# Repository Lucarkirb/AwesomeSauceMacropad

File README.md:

# AWESOME SAUCE MACROPAD

The best worst macropad I have ever made, for the world to see. 
Runs custom firmware that will support almost infinite layers, macros, and maybe even AHK support?

## What the hell is it?
It's a Seeed studio xiao rp2040 macro pad designed like a madman, with custom firmware thats coming real soon. 
The layout is a 3x3 + an extra 3 button thumb cluster that lets you add more common keys like layer shifters or modifiers. It also has an encoder that can work as what you want but also allows you to interact with the firmwares settings, along with an OLED display to do your bidding.

Currently, the project is a mess as the thing requires the KY-040 encoder breakout board instead of just an smt encoder and also requires a generic i2c oled screen you get for your arduinos.

## Can I get it? 
Go order it yourself, tho pcba is going to get pricy since the neo pixels are costly to handle in a factory. Luckily they are super easy to hand solder.

Currently, the project is still being manufactured as im writing this, and thus i dont have any way to write firmware. Stay tuned.

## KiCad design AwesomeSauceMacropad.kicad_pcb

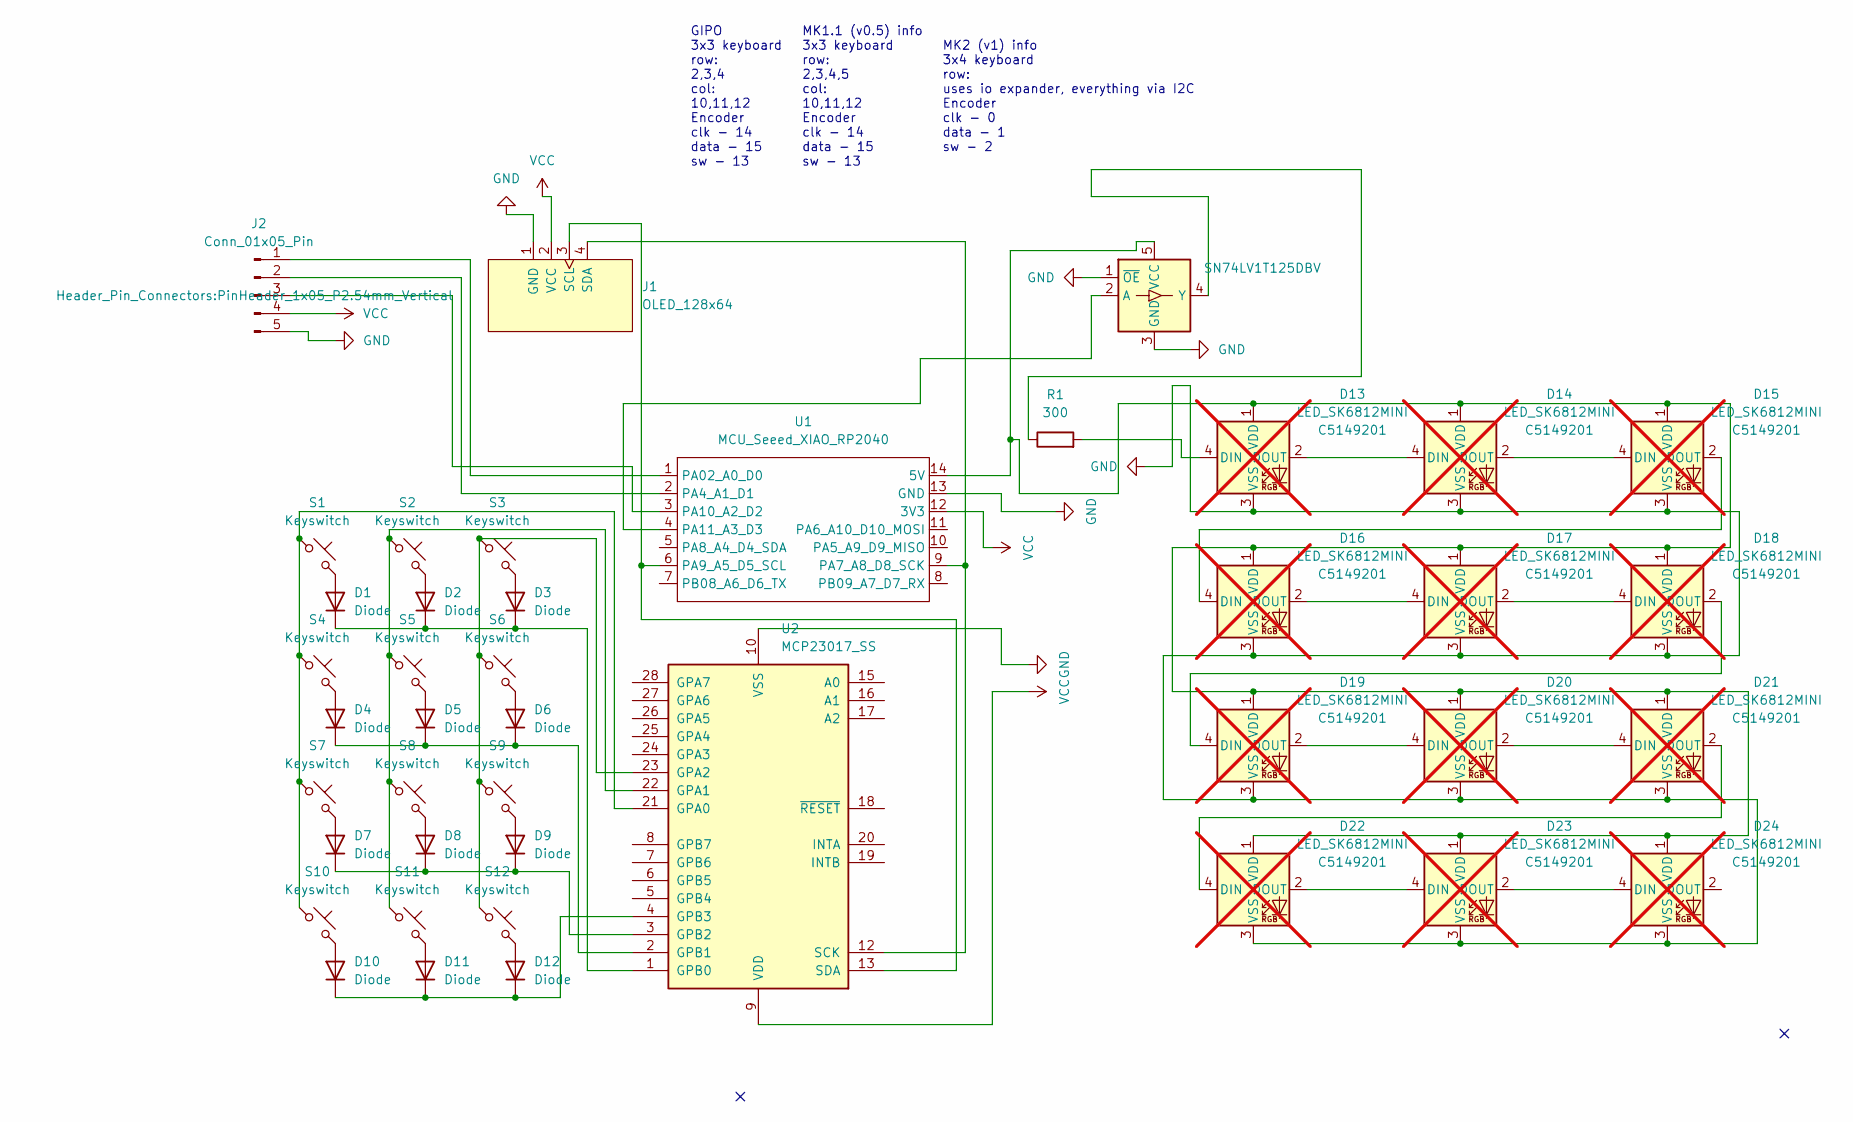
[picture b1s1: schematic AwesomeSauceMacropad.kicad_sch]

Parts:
D1, D2, D3, D4, D5, D6, D7, D8, D9, D10, D11, D12: Diode; Diode_SOD-123
D13, D14, D15, D16, D17, D18, D19, D20, D21, D22, D23, D24: LED_SK6812MINI; LCSC C5149201; not fitted
J1: OLED_128x64
J2: Conn_01x05_Pin; PinHeader_1x05_P2.54mm_Vertical
R1: 300; Resistor_0805
S1, S2, S3, S4, S5, S6, S7, S8, S9, S10, S11, S12: Keyswitch; Hotswap_Choc_V1V2_1.00u
U1: MCU_Seeed_XIAO_RP2040; Seeed_XIAO_RP2040
U2: MCP23017_SS; SSOP-28_5.3x10.2mm_P0.65mm
U3: SN74LV1T125DBV; SOT-23-5

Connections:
GND: D13.3 (VSS), D14.3 (VSS), D15.3 (VSS), D16.3 (VSS), D17.3 (VSS), D18.3 (VSS), D19.3 (VSS), D20.3 (VSS), D21.3 (VSS), D22.3 (VSS), D23.3 (VSS), D24.3 (VSS), J1.1 (GND), J2.5, U1.13 (GND), U2.10 (VSS), U3.1 (~OE), U3.3 (GND)
unnamed: D1.2 (A), S1.2
unnamed: D1.1 (K), D2.1 (K), D3.1 (K), U2.1 (GPB0)
unnamed: D2.2 (A), S2.2
unnamed: D3.2 (A), S3.2
unnamed: D4.2 (A), S4.2
unnamed: D4.1 (K), D5.1 (K), D6.1 (K), U2.2 (GPB1)
unnamed: D5.2 (A), S5.2
unnamed: D6.2 (A), S6.2
unnamed: D7.2 (A), S7.2
unnamed: D7.1 (K), D8.1 (K), D9.1 (K), U2.3 (GPB2)
unnamed: D8.2 (A), S8.2
unnamed: D9.2 (A), S9.2
unnamed: D10.2 (A), S10.2
unnamed: D10.1 (K), D11.1 (K), D12.1 (K), U2.4 (GPB3)
unnamed: D11.2 (A), S11.2
unnamed: D12.2 (A), S12.2
unnamed: D13.4 (DIN), R1.2
unnamed: D13.2 (DOUT), D14.4 (DIN)
unnamed: D13.1 (VDD), D14.1 (VDD), D15.1 (VDD), D16.1 (VDD), D17.1 (VDD), D18.1 (VDD), D19.1 (VDD), D20.1 (VDD), D21.1 (VDD), D22.1 (VDD), D23.1 (VDD), D24.1 (VDD), U1.14 (5V), U3.5 (VCC)
unnamed: D14.2 (DOUT), D15.4 (DIN)
unnamed: D15.2 (DOUT), D16.4 (DIN)
unnamed: D16.2 (DOUT), D17.4 (DIN)
unnamed: D17.2 (DOUT), D18.4 (DIN)
unnamed: D18.2 (DOUT), D19.4 (DIN)
unnamed: D19.2 (DOUT), D20.4 (DIN)
unnamed: D20.2 (DOUT), D21.4 (DIN)
unnamed: D21.2 (DOUT), D22.4 (DIN)
unnamed: D22.2 (DOUT), D23.4 (DIN)
unnamed: D23.2 (DOUT), D24.4 (DIN)
unnamed: J1.3 (SCL), U1.6 (PA9_A5_D5_SCL), U2.13 (SDA)
unnamed: J1.4 (SDA), U1.9 (PA7_A8_D8_SCK), U2.12 (SCK)
unnamed: J2.1, U1.1 (PA02_A0_D0)
unnamed: J2.2, U1.2 (PA4_A1_D1)
unnamed: J2.3, U1.3 (PA10_A2_D2)
unnamed: U1.4 (PA11_A3_D3), U3.2 (A)
unnamed: S1.1, S4.1, S7.1, S10.1, U2.21 (GPA0)
unnamed: S2.1, S5.1, S8.1, S11.1, U2.22 (GPA1)
unnamed: S3.1, S6.1, S9.1, S12.1, U2.23 (GPA2)
unnamed: R1.1, U3.4 (Y)
VCC: J1.2 (VCC), J2.4, U1.12 (3V3), U2.9 (VDD)

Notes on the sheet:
MK2 (v1) info 3x4 keyboard row: uses io expander, everything via I2C Encoder clk - 0 data - 1 sw - 2
GIPO 3x3 keyboard row: 2,3,4 col: 10,11,12 Encoder clk - 14 data - 15 sw - 13
MK1.1 (v0.5) info 3x3 keyboard row: 2,3,4,5 col: 10,11,12 Encoder clk - 14 data - 15 sw - 13

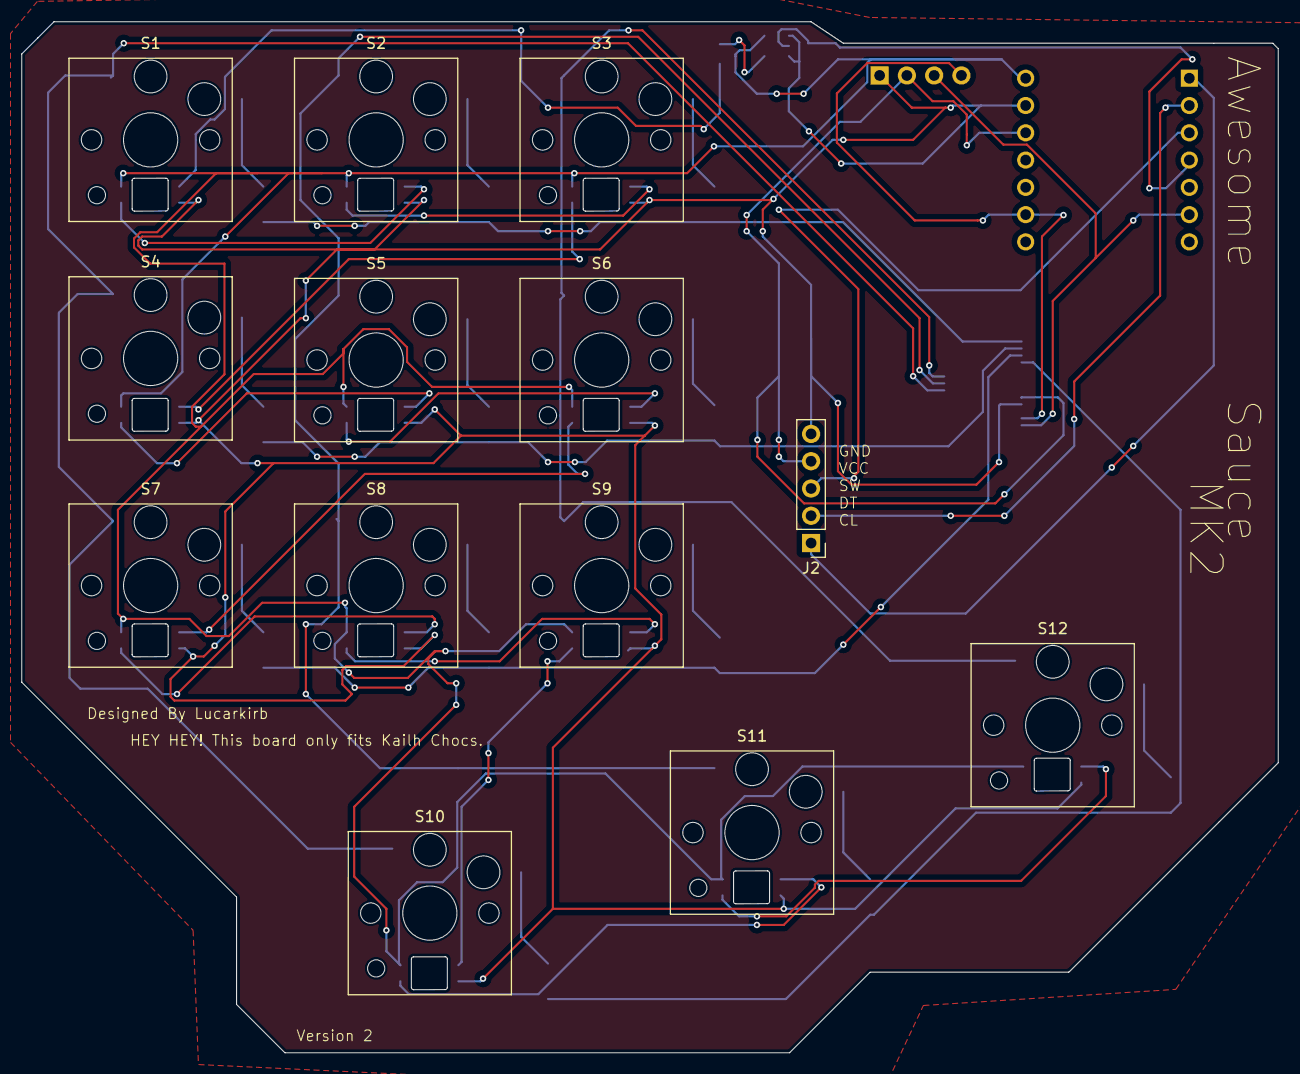
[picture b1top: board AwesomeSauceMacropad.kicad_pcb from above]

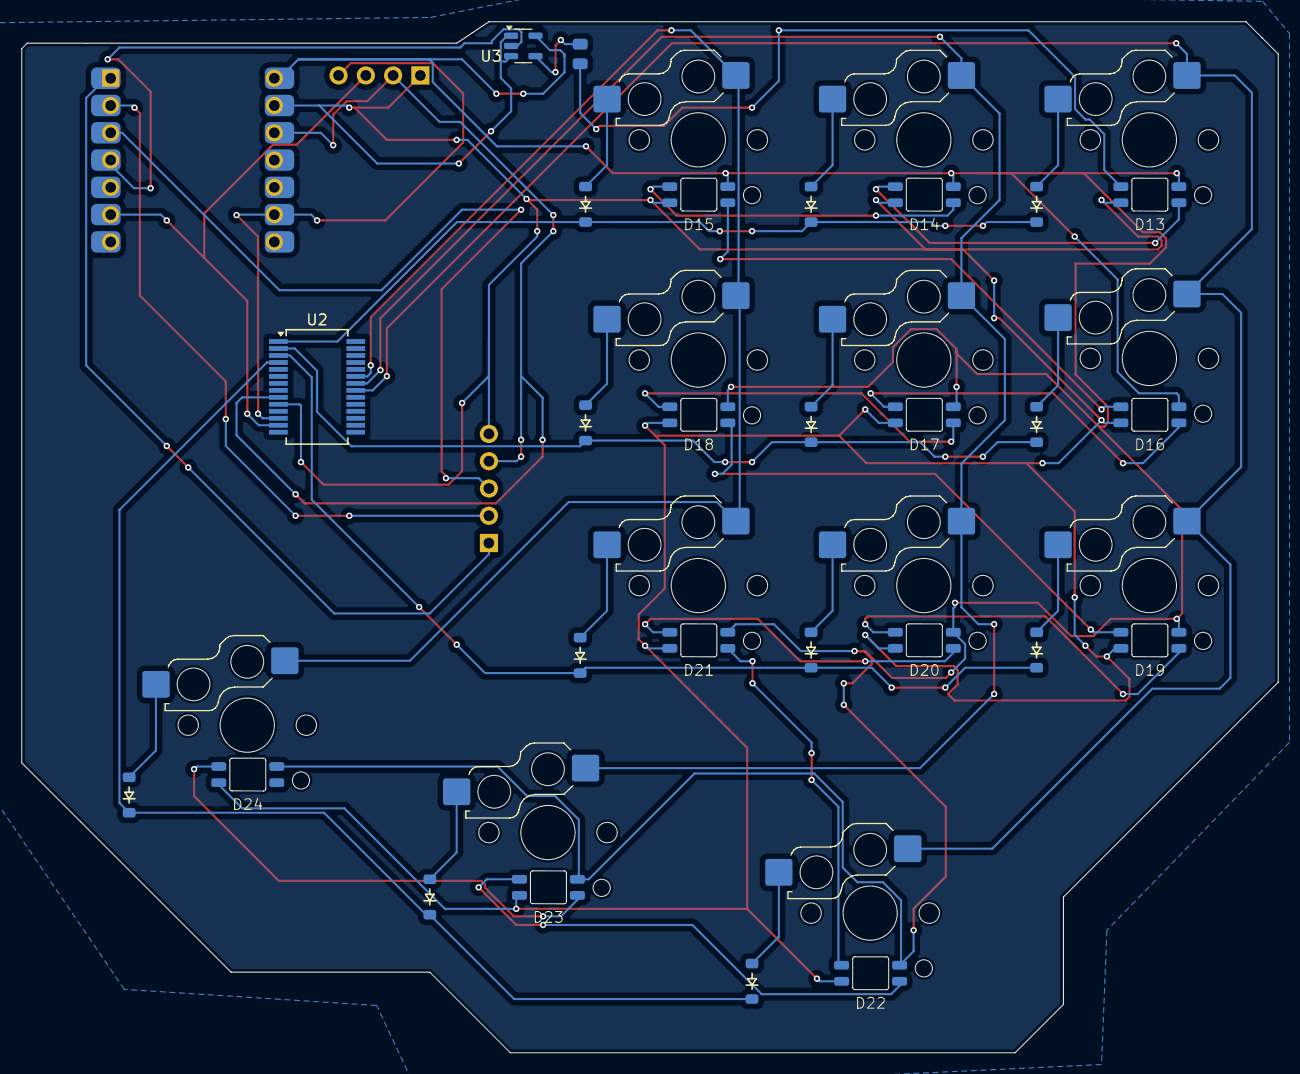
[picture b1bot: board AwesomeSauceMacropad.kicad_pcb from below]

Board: 2 copper layers, 117.0 x 96.0 mm, 42 parts (28 on the bottom side), 41 nets.

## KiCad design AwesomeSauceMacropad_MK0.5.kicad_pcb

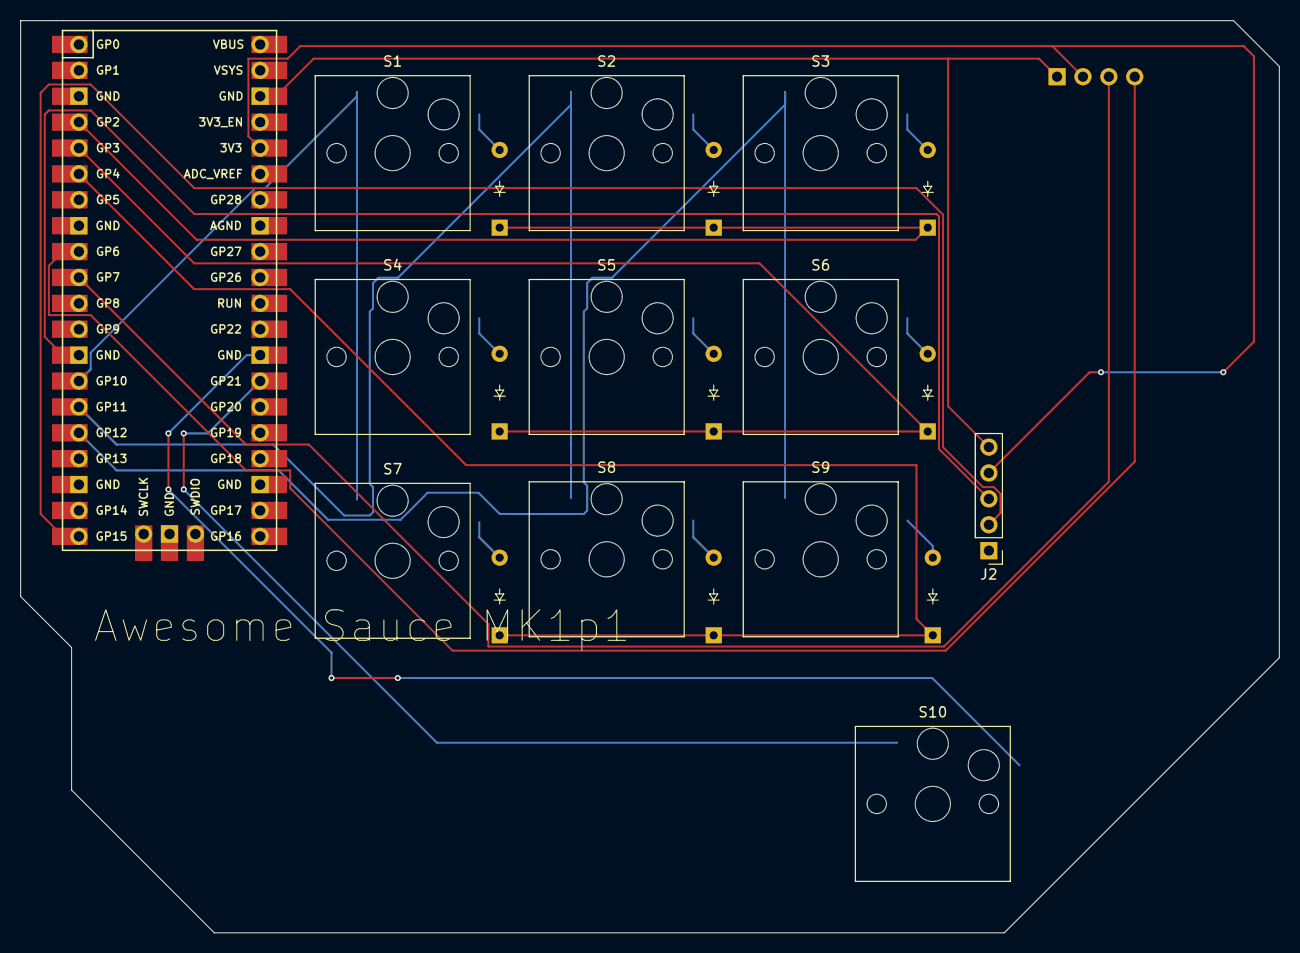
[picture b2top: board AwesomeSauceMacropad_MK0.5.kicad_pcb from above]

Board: 2 copper layers, 123.5 x 89.5 mm, 22 parts (0 on the bottom side), 24 nets.

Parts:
D1, D2, D3, D4, D5, D6, D7, D8, D9: Diode; Diode_DO-35
J1: OLED_128x64
J2: Conn_01x05_Pin; PinHeader_1x05_P2.54mm_Vertical
S1, S2, S3, S4, S5, S6, S7, S8, S9, S10: Keyswitch; Hotswap_Choc_V1_1.00u
U1: Raspberry_Pi_Pico

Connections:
GND: J1.1 (GND), J2.5, U1.38 (GND)
unnamed: D1.2 (A), S1.2
unnamed: D1.1 (K), D2.1 (K), D3.1 (K), U1.4 (GPIO2)
unnamed: D2.2 (A), S2.2
unnamed: D3.2 (A), S3.2
unnamed: D4.2 (A), S4.2
unnamed: D4.1 (K), D5.1 (K), D6.1 (K), U1.5 (GPIO3)
unnamed: D5.2 (A), S5.2
unnamed: D6.2 (A), S6.2
unnamed: D7.2 (A), S7.2
unnamed: D7.1 (K), D8.1 (K), D9.1 (K), U1.6 (GPIO4)
unnamed: D8.2 (A), S8.2
unnamed: D9.2 (A), S9.2
unnamed: J1.3 (SCL), U1.10 (GPIO7)
unnamed: J1.4 (SDA), U1.9 (GPIO6)
unnamed: J2.1, U1.19 (GPIO14)
unnamed: J2.2, U1.20 (GPIO15)
unnamed: J2.3, U1.13 (GND)
unnamed: S10.2, U1.28 (GND)
unnamed: S1.1, S4.1, S7.1, U1.14 (GPIO10)
unnamed: S2.1, S5.1, S8.1, U1.15 (GPIO11)
unnamed: S3.1, S6.1, S9.1, U1.16 (GPIO12)
unnamed: S10.1, U1.27 (GPIO21)
VCC: J1.2 (VCC), J2.4, U1.36 (3V3)

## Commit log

2025-09-26 added a blank readme
